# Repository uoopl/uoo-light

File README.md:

# uoo-light
IoT Light system

        Internet enabled light and electricity system based on nodeMCU and dedicated hardware

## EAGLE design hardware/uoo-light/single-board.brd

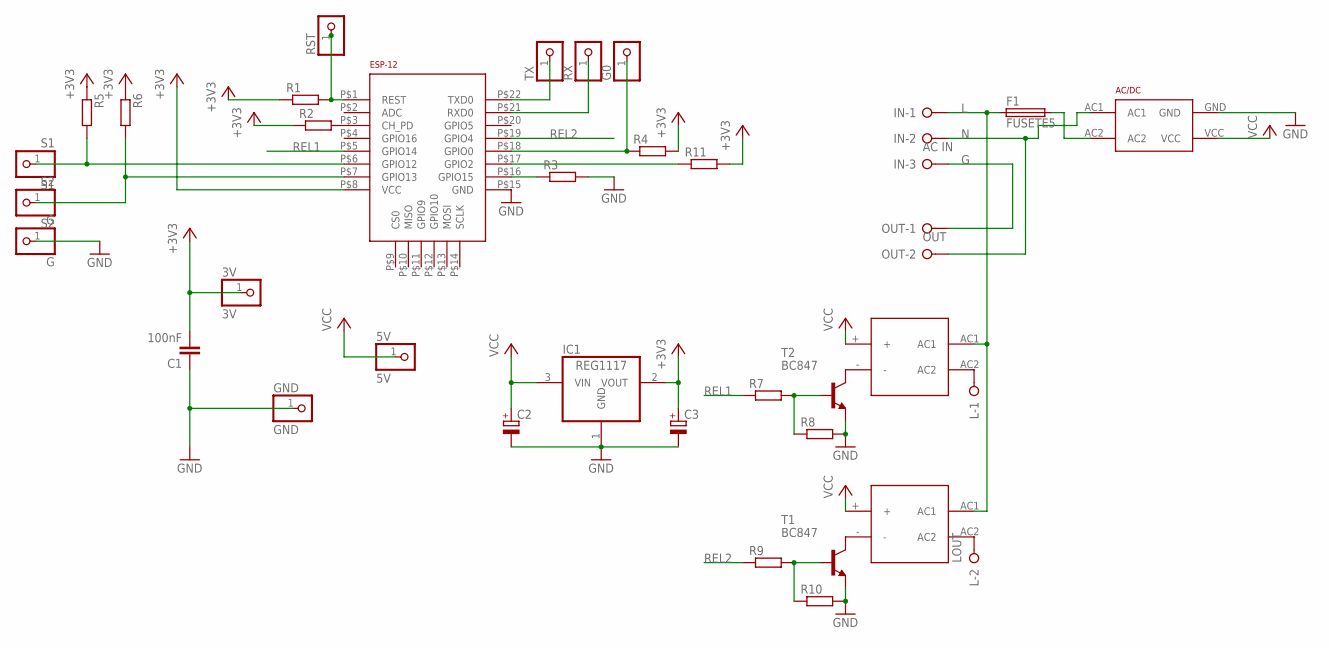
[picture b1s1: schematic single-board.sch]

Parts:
3V: 3V; 1X01
5V: 5V; 1X01
AC/DC: HLK-PM01
C1: 100nF; C0805K
C2, C3: CPOL-EUA/3216-18R; A/3216-18R
ESP-12: ESP-12EESP12E-SMD; ESP12E-SMD
F1: FUSETE5; TE5
G: G; 1X01
G0: PINHD-1X1; 1X01
GND: GND; 1X01
IC1: REG1117; SOT223
IN: AC IN; W237-133
L: LOUT; W237-132
OUT: OUT; W237-132
R1, R2, R3, R4, R5, R6, R7, R8, R9, R10, R11: R-EU_R0805; R0805
RST: PINHD-1X1; 1X01
RX: PINHD-1X1; 1X01
S1: S1; 1X01
S2: S2; 1X01
T1, T2: BC847; SOT23
TX: PINHD-1X1; 1X01
U$2, U$3: G3MB-202P

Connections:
+3V3: 3V.1, C1.2, C3.+, ESP-12.P$8 (VCC), IC1.2 (VOUT), R1.1, R2.1, R4.2, R5.1, R6.1, R11.2
G: IN.3, OUT.1
GND: AC/DC.GND, C1.1, C2.-, C3.-, ESP-12.P$15 (GND), G.1, GND.1, IC1.1 (GND), R3.2, R8.2, R10.2, T1.2 (E), T2.2 (E)
L: F1.1, IN.1, U$2.AC1, U$3.AC1
N: AC/DC.AC1, IN.2, OUT.2
unnamed: ESP-12.P$1 (REST), R1.2, RST.1
unnamed: ESP-12.P$3 (CH_PD), R2.2
unnamed: ESP-12.P$16 (GPIO15), R3.1
unnamed: ESP-12.P$18 (GPIO0), G0.1, R4.1
unnamed: ESP-12.P$22 (TXD0), TX.1
unnamed: ESP-12.P$21 (RXD0), RX.1
unnamed: AC/DC.AC2, F1.2
unnamed: L.2, U$3.AC2
unnamed: L.1, U$2.AC2
unnamed: T2.3 (C), U$2.-
unnamed: T1.3 (C), U$3.-
unnamed: R7.2, R8.1, T2.1 (B)
unnamed: R9.2, R10.1, T1.1 (B)
unnamed: ESP-12.P$17 (GPIO2), R11.1
REL1: ESP-12.P$5 (GPIO14), R7.1
REL2: ESP-12.P$19 (GPIO4), R9.1
SW1: ESP-12.P$6 (GPIO12), R5.2, S1.1
SW2: ESP-12.P$7 (GPIO13), R6.2, S2.1
VCC: 5V.1, AC/DC.VCC, C2.+, IC1.3 (VIN), U$2.+, U$3.+

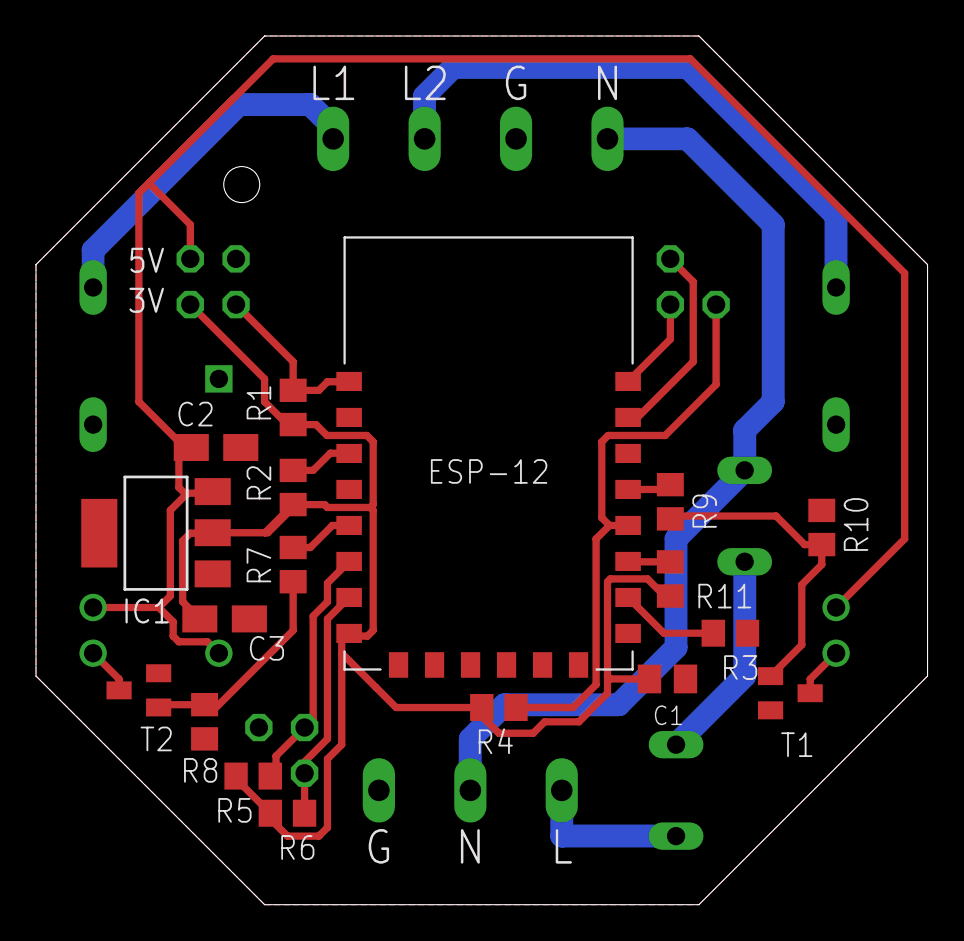
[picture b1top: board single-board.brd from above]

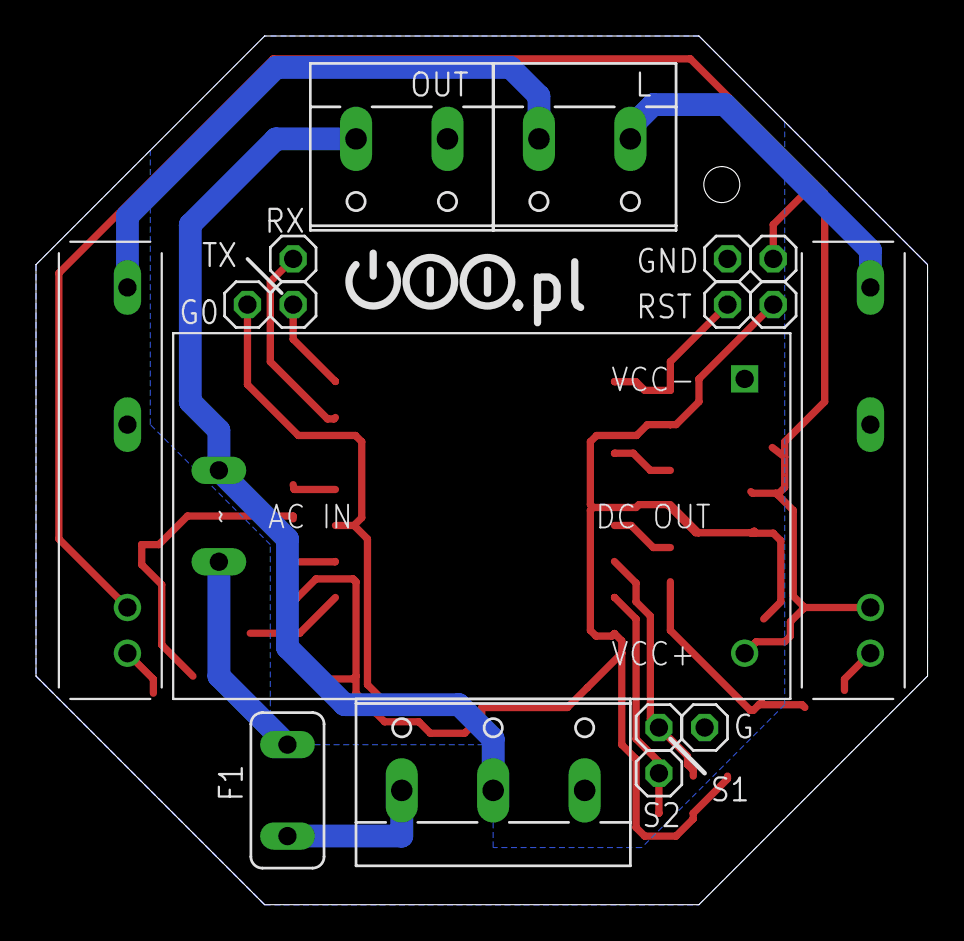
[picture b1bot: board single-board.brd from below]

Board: 2 copper layers, 49.5 x 48.3 mm, 35 parts (17 on the bottom side), 24 nets.

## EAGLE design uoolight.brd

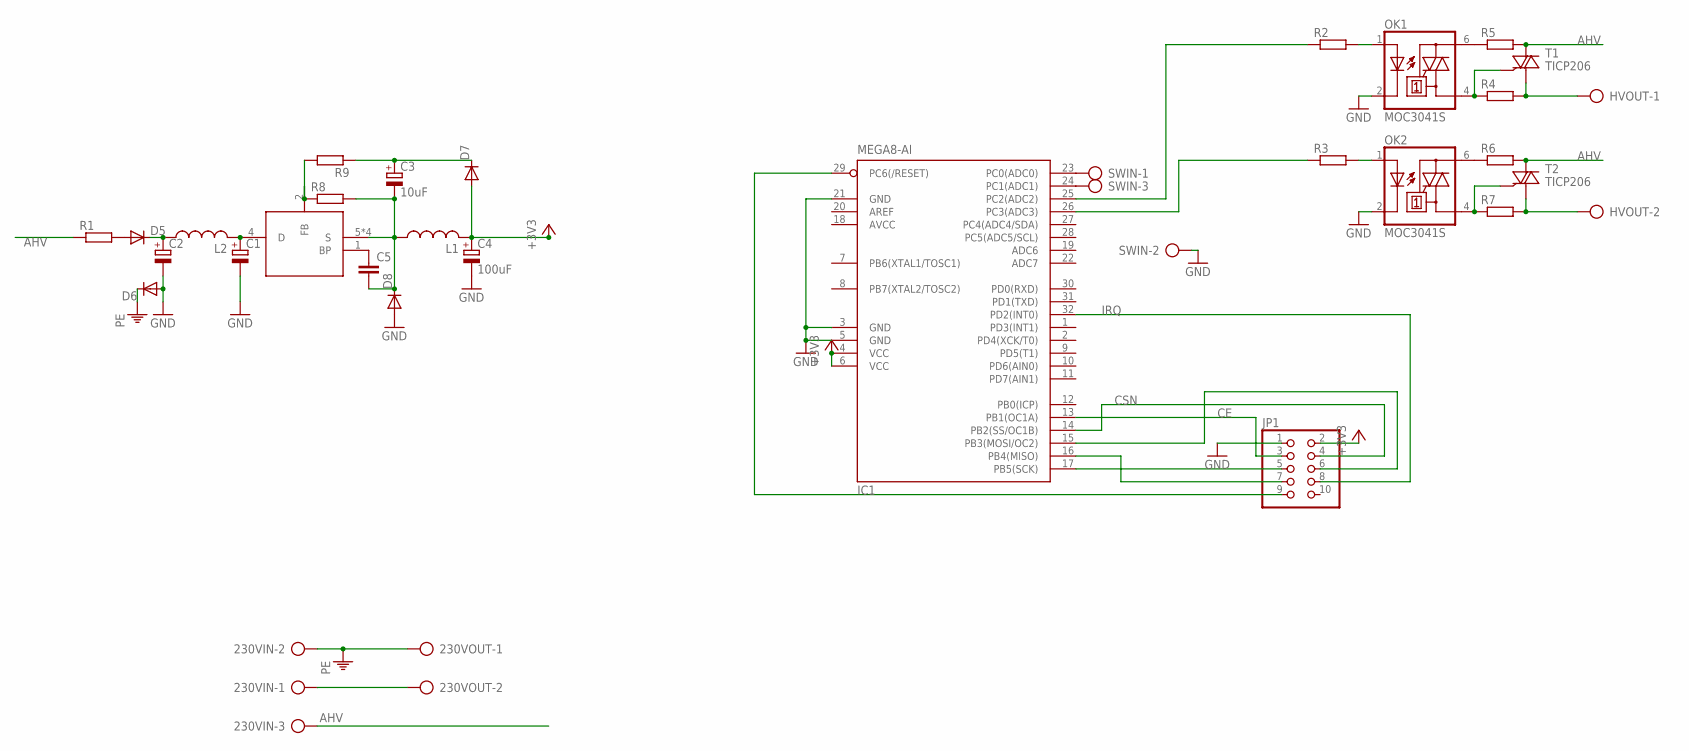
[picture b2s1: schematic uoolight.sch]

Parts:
230VIN: AK500/3
230VOUT: AK500/2
C1, C2: CPOL-EUE5-10.5; E5-10,5
C3: 10uF; 153CLV-0505
C4: 100uF; 153CLV-0605
C5: C-EUC0603K; C0603K
D5, D6, D7: DIODE-SOD323-W; SOD323-W
D8: DIODE-SOD123; SOD123
HVOUT: AK500/2
IC1: MEGA8-AI; TQFP32-08
JP1: PINHD-2X5; 2X05
L1, L2: L-USPIS2816; PIS2816
OK1, OK2: MOC3041S; DIL6-SMD
R1: R-EU_0309/12; 0309/12
R2, R3, R4, R5, R6, R7, R8, R9: R-EU_R0805; R0805
SWIN: AK500/3
T1, T2: TICP206; TO92-6
U$1: LNK304; SO8(SO-8C)

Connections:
+3V3: C4.+, D7.A, IC1.4 (VCC), IC1.6 (VCC), JP1.2, L1.2
AHV: 230VIN.3, R1.1, R5.2, R6.2, T1.A2, T2.A2
AVCC: IC1.18 (AVCC)
CE: IC1.13 (PB1(OC1A)), JP1.3
CSN: IC1.14 (PB2(SS/OC1B)), JP1.4
GND: C1.-, C2.-, C4.-, D6.A, D8.A, IC1.3 (GND), IC1.5 (GND), IC1.21 (GND), JP1.1, OK1.2 (C), OK2.2 (C), SWIN.2
HVG: 230VIN.1, 230VOUT.2
IRQ: IC1.32 (PD2(INT0)), JP1.8
MISO: IC1.16 (PB4(MISO)), JP1.7
MOSI: IC1.15 (PB3(MOSI/OC2)), JP1.6
unnamed: OK1.1 (A), R2.2
unnamed: D5.A, R1.2
unnamed: OK1.4 (A1), R4.1, T1.G
unnamed: HVOUT.1, R4.2, T1.A1
unnamed: OK1.6 (A2), R5.1
unnamed: IC1.23 (PC0(ADC0)), SWIN.1
unnamed: OK2.6 (A2), R6.1
unnamed: IC1.24 (PC1(ADC1)), SWIN.3
unnamed: OK2.4 (A1), R7.1, T2.G
unnamed: IC1.29 (PC6(/RESET)), JP1.9
unnamed: IC1.25 (PC2(ADC2)), R2.1
unnamed: HVOUT.2, R7.2, T2.A1
unnamed: IC1.26 (PC3(ADC3)), R3.1
unnamed: C3.-, C5.2, D8.C, L1.1, R8.2, U$1.5 (S), U$1.6 (S), U$1.7 (S), U$1.8 (S)
unnamed: C1.+, L2.2, U$1.4 (D)
unnamed: R8.1, R9.2, U$1.2 (FB)
unnamed: C2.+, D5.C, L2.1
unnamed: C3.+, D7.C, R9.1
unnamed: C5.1, U$1.1 (BP)
unnamed: OK2.1 (A), R3.2
PE: 230VIN.2, 230VOUT.1, D6.C
SCK: IC1.17 (PB5(SCK)), JP1.5

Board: 2 copper layers, 31 parts (0 on the bottom side), 31 nets, no tracks yet.

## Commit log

2016-02-13 First conception schematics
    First conception schematics and board (and backup files)
2016-04-13 single board hardware
2016-04-21 second version of board. Mirrored elecromagnetic reeds, shorter pads in esp-12, better paths.added mount hole, bigger holes in my elements in library.
